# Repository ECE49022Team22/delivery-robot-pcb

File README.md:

# Delivery Robot PCB

KiCad design files for the ECE49022 Team 22 senior design delivery robot control board.

This repository is the shared workspace for the board schematic, PCB layout, project libraries and design documentation.

## System overview

The current schematic includes an STM32F091RC microcontroller core, programming/debug and UART headers, reset and boot circuitry, clock and decoupling components, test points, and power conversion from 12 V to 5 V and 3.3 V. The 12 V input has a fuse, a reverse-battery P-FET, a TVS and a battery-voltage sense. The board also feeds four 5 V peripheral ports, a latch servo (half-duplex UART plus a fused battery feed), two MDD20A motor channels and two encoders, and links to the Raspberry Pi 5 (UART, AUX enable from the Pi 3V3, STM32 reset and BOOT0). An INA237 measures battery current on an off-board shunt (firmware counts charge) in the battery negative lead, and a buffered 5 V data line drives the payload-compartment WS2812B interior light.

The IMU (BNO085) is not on this board; it is wired to the robot off-board.

## Getting started

1. Install KiCad 10 with its standard symbol and footprint libraries.
2. Clone this repository.
3. Open delivery_robot_1.kicad_pro in KiCad Manager.
4. Open delivery_robot_1.kicad_sch to view the complete schematic. Use the Schematic Hierarchy panel to navigate between sheets.

Custom symbol and footprint libraries are included and registered in the project library tables. Keep the directory structure intact so project-relative library paths resolve.

## Repository contents

| Path | Purpose |
| --- | --- |
| delivery_robot_1.kicad_pro | Active KiCad project settings |
| delivery_robot_1.kicad_sch | Main board schematic |
| Buck_5V_2A.kicad_sch | Hierarchical 12 V to 5 V, 2 A buck sheet (TPS54202H, U3) |
| Buck_5V_6A.kicad_sch | Hierarchical 12 V to 5 V, 6 A buck sheet (TPS56637, U2), feeds the Pi 5 |
| Buck_5V_6A_AUX.kicad_sch | Second 12 V to 5 V, 6 A buck sheet (TPS56637, U5), +5V_AUX rail |
| LDO_3V3.kicad_sch | Hierarchical 3.3 V power supply sheet |
| Pi5_Interface.kicad_sch | Raspberry Pi 5 link J13 (6-pin JST XH: UART via R12/R13 1k, GND, Pi 3V3 for the AUX enable, STM32 reset Q2, BOOT0) and Pi power output J14 |
| GPIO_Breakout.kicad_sch | 2x8 2.54 mm expansion header J8 with spare MCU pins only: 1 +3V3, 2/16 GND, ADC (PC0/PA1/PA4), SPI2 (PB13 SCK, PC2 MISO, PB15 MOSI, PB9 CS), PWM (PC6/PC7), USART3 (PC10/PC11), I2C1 (PB6/PB7, now a shared bus with on-board 4.7k pull-ups R56/R57 and the INA237 U13 at 0x40). Unused MCU pins are no-connect. |
| Power_Indicators.kicad_sch | Green power LED per rail (+12V, +5V_PI, +5V_AUX, +5V_SYS, +3V3) and yellow STM32 debug LEDs (PA5, PB12, PB14) |
| Motor_Control.kicad_sch | MDD20A driver terminals (J6, J16) and encoder terminals (J7, J15) for two motors, PWM pull-downs, PTC on each driver ground, encoder buffers U9/U10 (74LVC2G17) with 1k + 1 nF filters, PTC-protected encoder supplies, USBLC6-4SC6 ESD arrays U6 (J6 + J16) and U7 (J7 + J15), STM32 pin table |
| Test_Points.kicad_sch | Power test points: J5 1x06 2.54 mm header (+12V, GND, +5V_AUX, +5V_SYS, +3V3, +3.3VA) and TP3 scope GND loop |
| Input_Protection.kicad_sch | Reverse-battery P-FET Q1 with gate clamp, SMBJ16A TVS D13 on +12V, battery-voltage divider to PA0 |
| AUX_Outputs.kicad_sch | Four +5V_AUX peripheral ports J18-J21 (top-entry JST XH), one 1.5 A PTC each |
| Servo_Interface.kicad_sch | Latch servo port J17 (fused battery feed for an external buck, half-duplex UART through U8 SN74LVC1T45) |
| Battery_Monitor.kicad_sch | Battery current monitor: U13 INA237 on an off-board 50 A / 75 mV shunt in the battery - lead (Kelvin sense on J23), 10R/100 nF input filter, I2C1 on PB6/PB7 at 0x40, ALERT to PB4, VBUS on +12V |
| Interior_Light.kicad_sch | Payload-compartment WS2812B light J24 (3-pin top-entry JST XH): +5V_AUX through PTC F12, U14 SN74LV1T125 buffers PB5 (SPI1_MOSI) data to 5 V, D16 ESD |
| delivery_robot_1.pdf | Plot of all schematic sheets, regenerated automatically on every schematic commit |
| tools/hooks/ | Git hooks (pre-commit regenerates the schematic PDF) |
| libs/ | Project libraries: custom buck converter symbols/footprints, and project_symbols.kicad_sym (STM32F091RCTx and Crystal_GND24 frozen at the versions this design uses) |
| LDO_KiCad/ | Reusable LDO example, libraries and footprint review |
| sym-lib-table, fp-lib-table | Project-specific library configuration |
| docs/ | Subsystem documentation and design notes |
| validation/ | Connectivity checks and reference netlist |
| system-ERC-report.txt | Saved electrical rules check results |
| system-netlist.xml | Exported system connectivity |
| system-preview/ | Rendered schematic sheets |
| received-project-settings/ | Archived initial settings; not the active project |

Power supply details are documented in [docs/power-supply.md](docs/power-supply.md). Earlier simulation notes are in [STM32-LDO-design.md](STM32-LDO-design.md).

The 2026-10-15 design review changes are summarized in [docs/design-review-2026-10-15.md](docs/design-review-2026-10-15.md). The 2026-10-27 battery current monitor and interior light are described in [docs/design-change-2026-10-27.md](docs/design-change-2026-10-27.md).

Component-selection rationale is in [docs/passive-selection-review.md](docs/passive-selection-review.md), [docs/clock-selection.md](docs/clock-selection.md) and [docs/fuse-selection.md](docs/fuse-selection.md). The fuse selection includes both the PCB-mounted holder and its separately purchased insert.

## Design status

Schematic: ERC is clean (0 errors, 0 warnings). PCB: 100 x 100 mm, 4 layers with an In1 GND plane. The board was fully routed as of commit 789cabe (2026-10-26), including outer-layer GND pours with stitching vias and widened high-current paths.

The `feat/battery-monitor-interior-light` branch (2026-10-27) added 18 parts: U13, U14, J23, J24, F12, D16, R54-R60 and C52-C56. They are placed and routed. DRC is clean, with 0 unconnected and 0 schematic parity issues. Layout notes are in [docs/design-change-2026-10-27.md](docs/design-change-2026-10-27.md#layout).

The saved ERC report and netlist (system-ERC-report.txt, system-netlist.xml) were regenerated on 2026-10-28 with KiCad 10.0.6 for the INA237 / 5.10 V change (ERC: 0 errors, 0 warnings). validation/verify_2026_10_27.py checks the branch against the netlist of its parent commit. validation/verify_integration.py checks against the older October 5 connectivity.

Saved reports describe the checked revision. Regenerate them after relevant design changes.

## Team workflow

- Use the active delivery_robot_1 project for board work.
- Pull current changes before editing and coordinate ownership of schematic sheets and the PCB.
- Work on branches and review changes before merging.
- Save files in KiCad before committing. Include required project-local libraries with design changes.
- Run ERC after schematic changes and DRC after layout changes. Review outstanding findings before ordering boards.
- Enable the repository hooks once per clone with `git config core.hooksPath tools/hooks`. The pre-commit hook then re-plots delivery_robot_1.pdf from the staged schematic files and adds it to any commit that changes a `.kicad_sch` or `.kicad_pro` file. It needs KiCad installed; set `KICAD_CLI` if kicad-cli is not in the default location.

Editing locks, local UI settings and automatic backups are excluded from Git. Edit the native KiCad sources directly; regenerating files from older scripts may overwrite manual changes.

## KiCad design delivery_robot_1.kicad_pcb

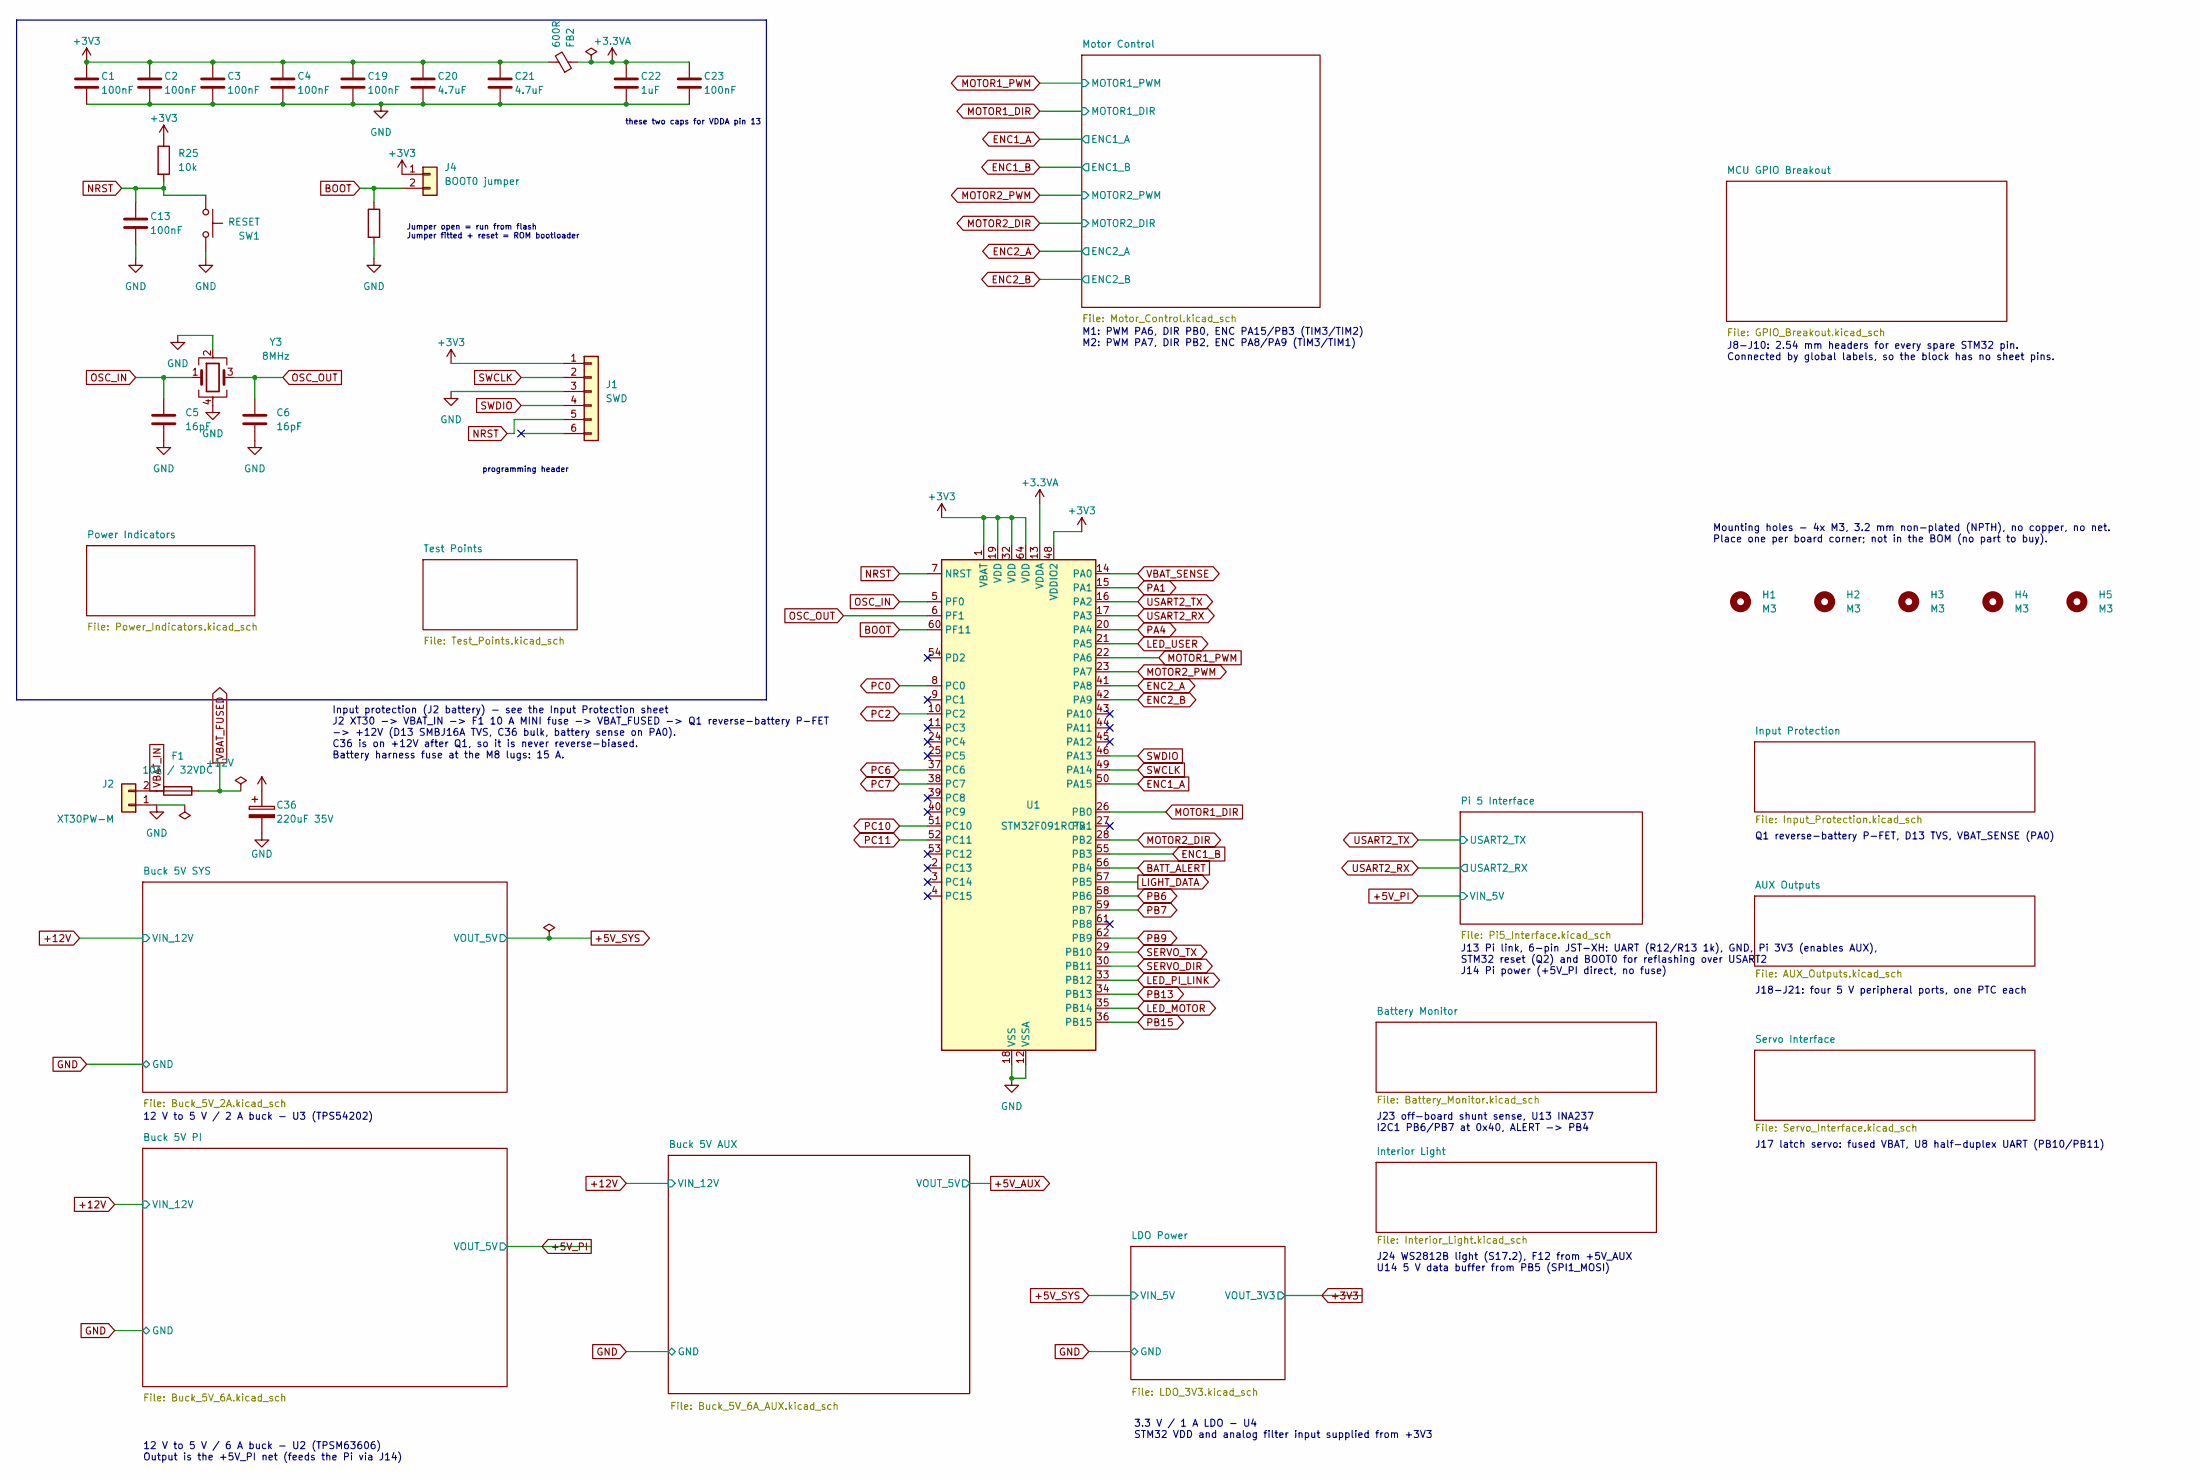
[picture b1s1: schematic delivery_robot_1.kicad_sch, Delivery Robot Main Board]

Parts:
C1, C2, C3, C4, C13, C19, C23: 100nF; C_0805_2012Metric
C5, C6: 16pF; C_0805_2012Metric; MPN C0805C160J5GACTU
C20, C21: 4.7uF; C_0805_2012Metric
C22: 1uF; C_0805_2012Metric
C36: 220uF 35V; CP_Radial_D8.0mm_P3.50mm; MPN EEU-FR1V221
F1: 10A / 32VDC; Fuseholder_Blade_Mini_Keystone_3568; MPN 3568
FB2: 600R; L_0805_2012Metric; MPN BLM21PG601SN1D
H1, H2, H3, H4, H5: M3; MountingHole_3.2mm_M3
J1: SWD; PinHeader_1x06_P2.54mm_Vertical
J2: XT30PW-M; AMASS_XT30PW-M_1x02_P2.50mm_Horizontal; MPN XT30PW-M
J4: BOOT0 jumper; PinHeader_1x02_P2.54mm_Vertical
R1, R25: 10k; R_0805_2012Metric
SW1: RESET; SW_SPST_PTS810
U1: STM32F091RCTx; LQFP-64_10x10mm_P0.5mm
Y3: 8MHz; Crystal_SMD_Abracon_ABM3B-4Pin_5.0x3.2mm; MPN ABM3B-8.000MHZ-B2-T

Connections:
+3.3VA: C22.1, C23.1, FB2.1, U1.13 (VDDA); also elsewhere on the board
+3V3: C1.1, C2.1, C3.1, C4.1, C19.1, C20.1, C21.1, FB2.2, J1.1, J4.1, R25.1, U1.1 (VBAT), U1.19 (VDD), U1.32 (VDD), U1.48 (VDDIO2), U1.64 (VDD); also elsewhere on the board
+12V: C36.1; also elsewhere on the board
BATT_ALERT: U1.56 (PB4); also elsewhere on the board
BOOT: J4.2, R1.1, U1.60 (PF11); also elsewhere on the board
ENC1_A: U1.50 (PA15); also elsewhere on the board
ENC1_B: U1.55 (PB3); also elsewhere on the board
ENC2_A: U1.41 (PA8); also elsewhere on the board
ENC2_B: U1.42 (PA9); also elsewhere on the board
GND: C1.2, C2.2, C3.2, C4.2, C5.2, C6.2, C13.2, C19.2, C20.2, C21.2, C22.2, C23.2, C36.2, J1.3, J2.1, R1.2, SW1.2, U1.12 (VSSA), U1.18 (VSS), U1.31 (VSS), U1.47 (VSS), U1.63 (VSS), Y3.2, Y3.4; also elsewhere on the board
LED_MOTOR: U1.35 (PB14); also elsewhere on the board
LED_PI_LINK: U1.33 (PB12); also elsewhere on the board
LED_USER: U1.21 (PA5); also elsewhere on the board
LIGHT_DATA: U1.57 (PB5); also elsewhere on the board
MOTOR1_DIR: U1.26 (PB0); also elsewhere on the board
MOTOR1_PWM: U1.22 (PA6); also elsewhere on the board
MOTOR2_DIR: U1.28 (PB2); also elsewhere on the board
MOTOR2_PWM: U1.23 (PA7); also elsewhere on the board
NRST: C13.1, J1.5, R25.2, SW1.1, U1.7 (NRST); also elsewhere on the board
OSC_IN: C5.1, U1.5 (PF0), Y3.1
OSC_OUT: C6.1, U1.6 (PF1), Y3.3
PA1: U1.15 (PA1); also elsewhere on the board
PA4: U1.20 (PA4); also elsewhere on the board
PB6: U1.58 (PB6); also elsewhere on the board
PB7: U1.59 (PB7); also elsewhere on the board
PB9: U1.62 (PB9); also elsewhere on the board
PB13: U1.34 (PB13); also elsewhere on the board
PB15: U1.36 (PB15); also elsewhere on the board
PC0: U1.8 (PC0); also elsewhere on the board
PC2: U1.10 (PC2); also elsewhere on the board
PC6: U1.37 (PC6); also elsewhere on the board
PC7: U1.38 (PC7); also elsewhere on the board
PC10: U1.51 (PC10); also elsewhere on the board
PC11: U1.52 (PC11); also elsewhere on the board
SERVO_DIR: U1.30 (PB11); also elsewhere on the board
SERVO_TX: U1.29 (PB10); also elsewhere on the board
SWCLK: J1.2, U1.49 (PA14)
SWDIO: J1.4, U1.46 (PA13)
USART2_RX: U1.17 (PA3); also elsewhere on the board
USART2_TX: U1.16 (PA2); also elsewhere on the board
VBAT_FUSED: F1.1; also elsewhere on the board
VBAT_IN: F1.2, J2.2
VBAT_SENSE: U1.14 (PA0); also elsewhere on the board

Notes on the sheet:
J24 WS2812B light (S17.2), F12 from +5V_AUX U14 5 V data buffer from PB5 (SPI1_MOSI)
J13 Pi link, 6-pin JST-XH: UART (R12/R13 1k), GND, Pi 3V3 (enables AUX), STM32 reset (Q2) and BOOT0 for reflashing over USART2 J14 Pi power (+5V_PI direct, no fuse)
Jumper open = run from flash Jumper fitted + reset = ROM bootloader
J17 latch servo: fused VBAT, U8 half-duplex UART (PB10/PB11)
M1: PWM PA6, DIR PB0, ENC PA15/PB3 (TIM3/TIM2) M2: PWM PA7, DIR PB2, ENC PA8/PA9 (TIM3/TIM1)
programming header
J18-J21: four 5 V peripheral ports, one PTC each
3.3 V / 1 A LDO - U4 STM32 VDD and analog filter input supplied from +3V3
J8-J10: 2.54 mm headers for every spare STM32 pin. Connected by global labels, so the block has no sheet pins.
J23 off-board shunt sense, U13 INA237 I2C1 PB6/PB7 at 0x40, ALERT -> PB4
Mounting holes - 4x M3, 3.2 mm non-plated (NPTH), no copper, no net. Place one per board corner; not in the BOM (no part to buy).
Q1 reverse-battery P-FET, D13 TVS, VBAT_SENSE (PA0)
these two caps for VDDA pin 13
Input protection (J2 battery) - see the Input Protection sheet J2 XT30 -> VBAT_IN -> F1 10 A MINI fuse -> VBAT_FUSED -> Q1 reverse-battery P-FET -> +12V (D13 SMBJ16A TVS, C36 bulk, battery sense on PA0). C36 is on +12V after Q1, so it is never reverse-biased. Battery harness fuse at the M8 lugs: 15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
12 V to 5 V / 2 A buck - U3 (TPS54202)
12 V to 5 V / 6 A buck - U2 (TPSM63606) Output is the +5V_PI net (feeds the Pi via J14)

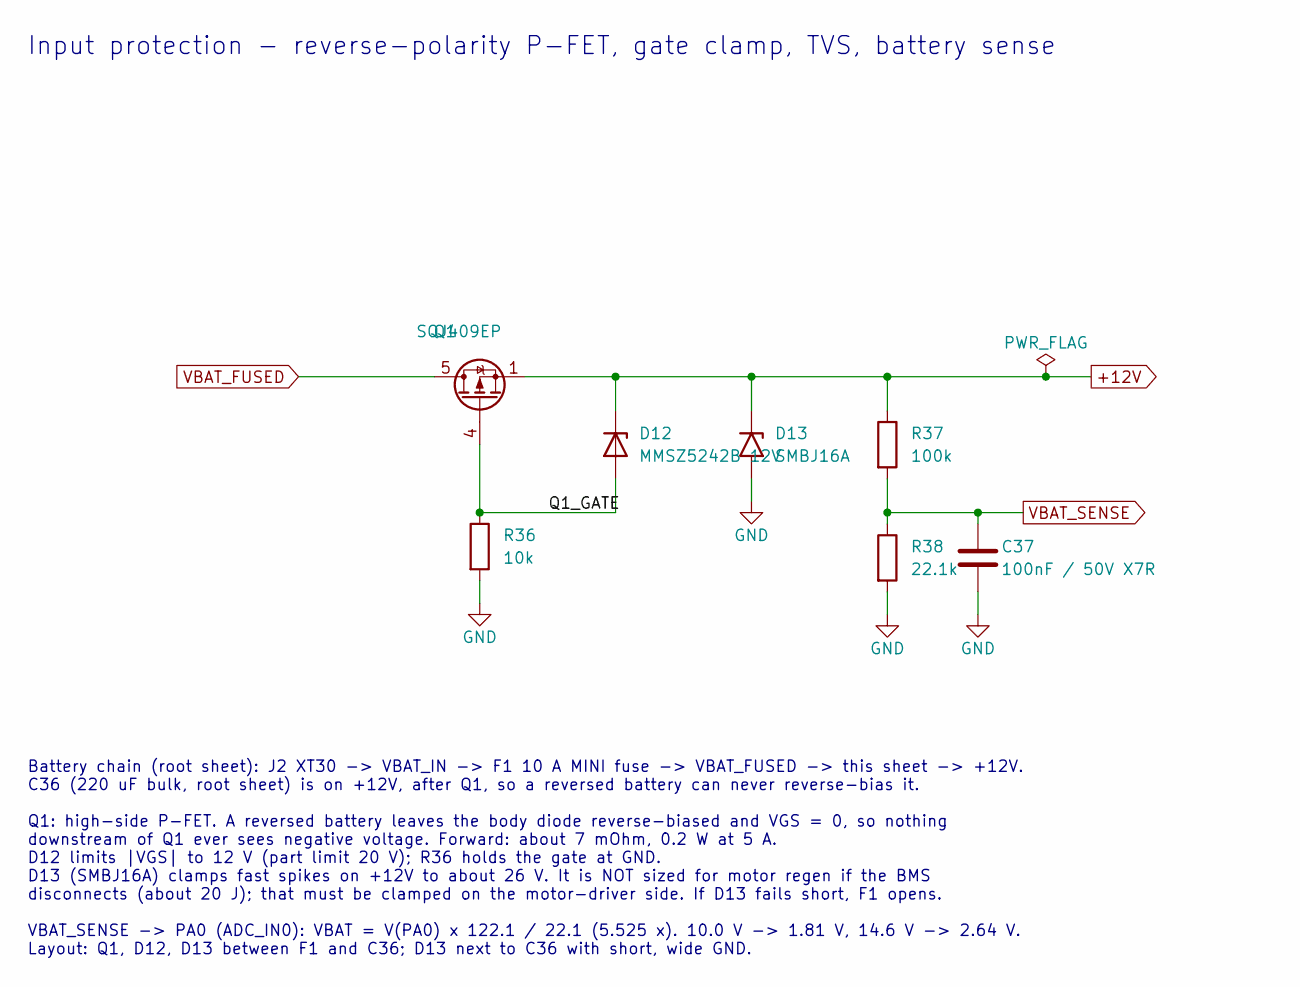
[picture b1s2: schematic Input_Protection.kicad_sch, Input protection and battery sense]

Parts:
C37: 100nF / 50V X7R; C_0805_2012Metric; MPN C0805C104K5RACTU
D12: MMSZ5242B 12V; D_SOD-123; MPN MMSZ5242BT1G
D13: SMBJ16A; D_SMB; MPN SMBJ16A
Q1: SQJ409EP; PowerPAK_SO-8L_Single; MPN SQJ409EP-T1_BE3
R36: 10k; R_0805_2012Metric
R37: 100k; R_0805_2012Metric; Tolerance 1%
R38: 22.1k; R_0805_2012Metric; Tolerance 1%

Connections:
+12V: D12.1 (K), D13.1 (A1), Q1.1 (S), Q1.2 (S), Q1.3 (S), R37.1; also elsewhere on the board
/Input Protection/Q1_GATE: D12.2 (A), Q1.4 (G), R36.1
GND: C37.2, D13.2 (A2), R36.2, R38.2; also elsewhere on the board
VBAT_FUSED: Q1.5 (D); also elsewhere on the board
VBAT_SENSE: C37.1, R37.2, R38.1; also elsewhere on the board

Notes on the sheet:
Battery chain (root sheet): J2 XT30 -> VBAT_IN -> F1 10 A MINI fuse -> VBAT_FUSED -> this sheet -> +12V. C36 (220 uF bulk, root sheet) is on +12V, after Q1, so a reversed battery can never reverse-bias it. Q1: high-side P-FET. A reversed battery leaves the body diode reverse-biased and VGS = 0, so 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
Input protection - reverse-polarity P-FET, gate clamp, TVS, battery sense

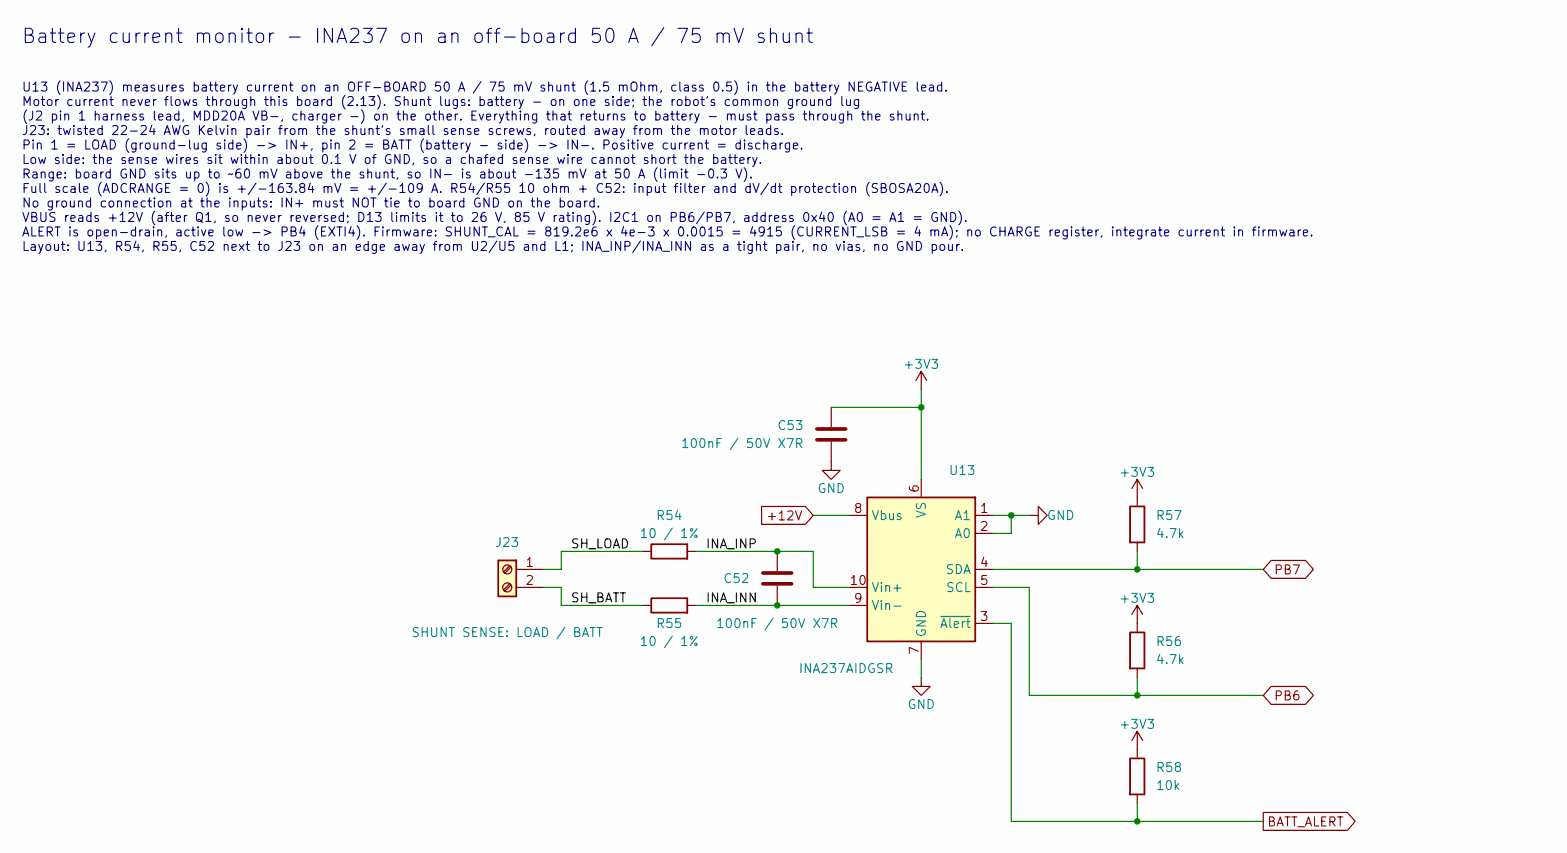
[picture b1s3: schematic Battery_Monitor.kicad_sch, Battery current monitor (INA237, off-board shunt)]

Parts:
C52, C53: 100nF / 50V X7R; C_0805_2012Metric; MPN C0805C104K5RACTU
J23: SHUNT SENSE: LOAD / BATT; TerminalBlock_Phoenix_MPT-0,5-2-2.54_1x02_P2.54mm_Horizontal; MPN 1725656
R54, R55: 10 / 1%; R_0805_2012Metric; Tolerance 1%; MPN RC0805FR-0710RL
R56, R57: 4.7k; R_0805_2012Metric; Tolerance 1%; MPN RC0805FR-074K7L
R58: 10k; R_0805_2012Metric; Tolerance 1%; MPN RC0805FR-0710KL
U13: INA237AIDGSR; TSSOP-10_3x3mm_P0.5mm; MPN INA237AIDGSR

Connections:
+3V3: C53.1, R56.1, R57.1, R58.1, U13.6 (VS); also elsewhere on the board
+12V: U13.8 (Vbus); also elsewhere on the board
/Battery Monitor/INA_INN: C52.2, R55.2, U13.9 (Vin-)
/Battery Monitor/INA_INP: C52.1, R54.2, U13.10 (Vin+)
/Battery Monitor/SH_BATT: J23.2, R55.1
/Battery Monitor/SH_LOAD: J23.1, R54.1
BATT_ALERT: R58.2, U13.3 (~Alert); also elsewhere on the board
GND: C53.2, U13.1 (A1), U13.2 (A0), U13.7 (GND); also elsewhere on the board
PB6: R56.2, U13.5 (SCL); also elsewhere on the board
PB7: R57.2, U13.4 (SDA); also elsewhere on the board

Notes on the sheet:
Battery current monitor - INA237 on an off-board 50 A / 75 mV shunt
U13 (INA237) measures battery current on an OFF-BOARD 50 A / 75 mV shunt (1.5 mOhm, class 0.5) in the battery NEGATIVE lead. Motor current never flows through this board (2.13). Shunt lugs: battery - on one side; the robot's common ground lug (J2 pin 1 harness lead, MDD20A VB-, charger -) on the ot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

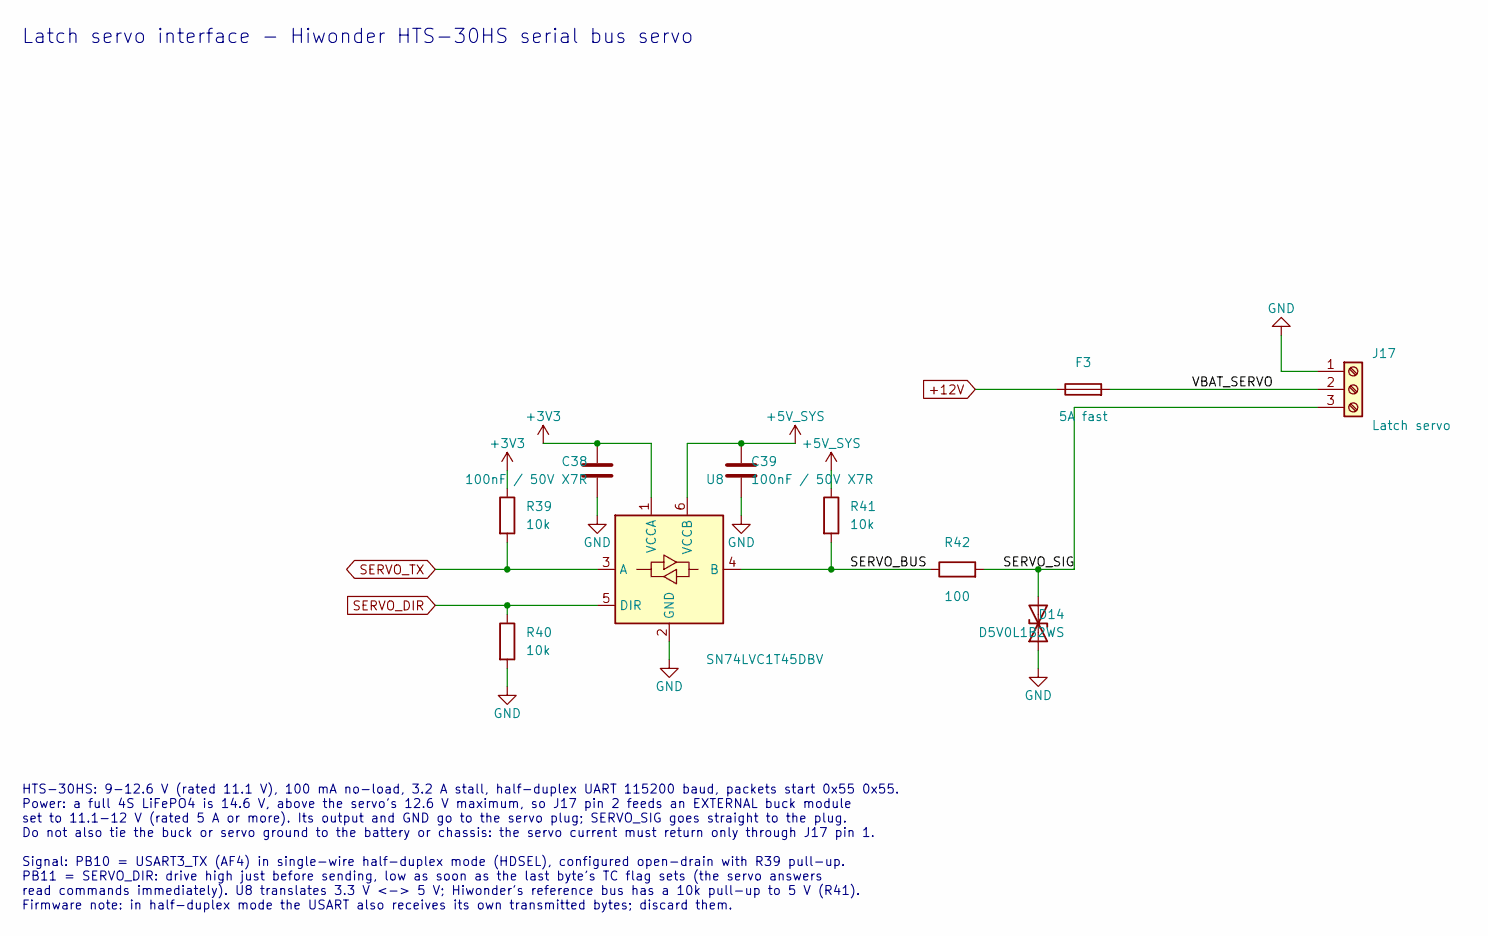
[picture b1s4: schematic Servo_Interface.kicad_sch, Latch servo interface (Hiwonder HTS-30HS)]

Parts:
C38, C39: 100nF / 50V X7R; C_0805_2012Metric; MPN C0805C104K5RACTU
D14: D5V0L1B2WS; D_SOD-323; MPN D5V0L1B2WS-7
F3: 5A fast; Fuse_Littelfuse-NANO2-451_453; MPN 0451005.MRL
J17: Latch servo; TerminalBlock_Phoenix_MKDS-1,5-3_1x03_P5.00mm_Horizontal; MPN 1715035 (MKDS 1,5/3, 5.0 mm pitch)
R39, R40, R41: 10k; R_0805_2012Metric
R42: 100; R_0805_2012Metric
U8: SN74LVC1T45DBV; SOT-23-6; MPN SN74LVC1T45DBVR

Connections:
+3V3: C38.1, R39.1, U8.1 (VCCA); also elsewhere on the board
+5V_SYS: C39.1, R41.1, U8.6 (VCCB); also elsewhere on the board
+12V: F3.1; also elsewhere on the board
/Servo Interface/SERVO_BUS: R41.2, R42.1, U8.4 (B)
/Servo Interface/SERVO_SIG: D14.2 (A2), J17.3, R42.2
/Servo Interface/VBAT_SERVO: F3.2, J17.2
GND: C38.2, C39.2, D14.1 (A1), J17.1, R40.2, U8.2 (GND); also elsewhere on the board
SERVO_DIR: R40.1, U8.5 (DIR); also elsewhere on the board
SERVO_TX: R39.2, U8.3 (A); also elsewhere on the board

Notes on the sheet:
Latch servo interface - Hiwonder HTS-30HS serial bus servo
HTS-30HS: 9-12.6 V (rated 11.1 V), 100 mA no-load, 3.2 A stall, half-duplex UART 115200 baud, packets start 0x55 0x55. Power: a full 4S LiFePO4 is 14.6 V, above the servo's 12.6 V maximum, so J17 pin 2 feeds an EXTERNAL buck module set to 11.1-12 V (rated 5 A or more). Its output and GND go to the 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

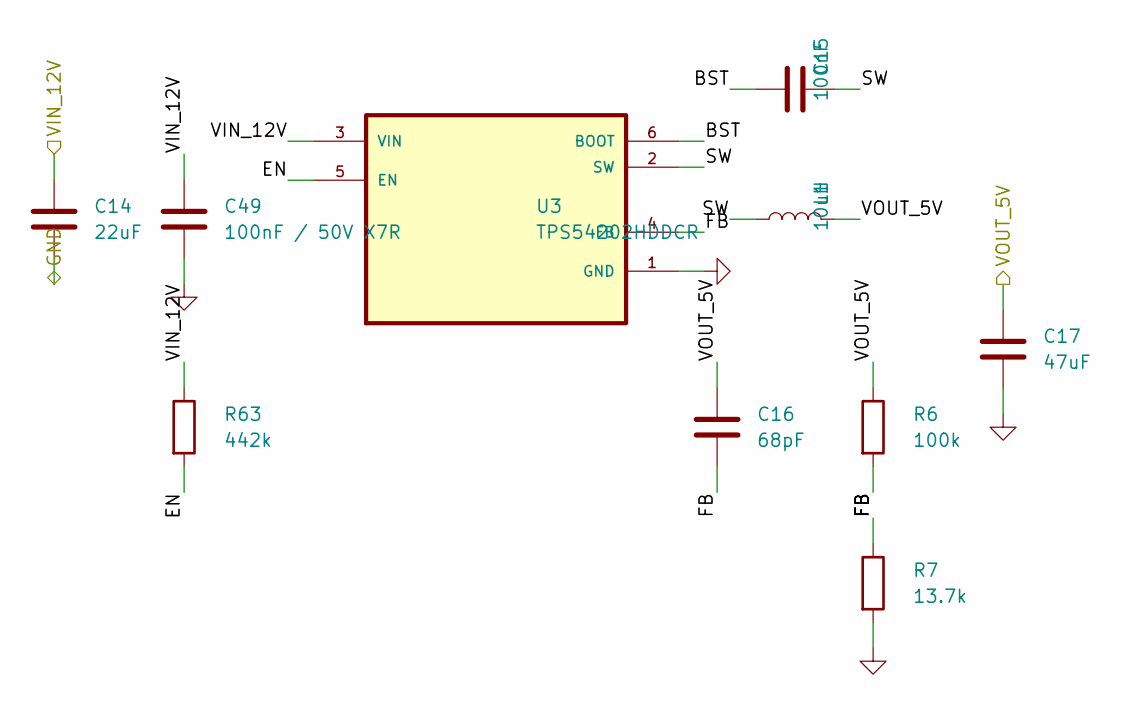
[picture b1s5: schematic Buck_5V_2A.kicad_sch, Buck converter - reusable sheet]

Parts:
C14: 22uF; C_1210_3225Metric; MPN GRM32ER61E226KE15L
C15: 100nF; C_0805_2012Metric; MPN C0805C104K5RACTU
C16: 68pF; C_0805_2012Metric; MPN C0805C680J5GACTU
C17: 47uF; C_1210_3225Metric; MPN GRM32ER61C476KE15L
C49: 100nF / 50V X7R; C_0805_2012Metric; MPN C0805C104K5RACTU
L1: 10uH; L_TDK_VLS6045EX_VLS6045AF; MPN VLS6045EX-100M
R6: 100k; R_0805_2012Metric; MPN RC0805FR-07100KL
R7: 13.7k; R_0805_2012Metric; MPN RC0805FR-0713K7L
R63: 442k; R_0805_2012Metric; MPN RC0805FR-07442KL
U3: TPS54202HDDCR; SOT95P280X110-6N; MPN TPS54202HDDCR

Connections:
+5V_SYS: C16.1, C17.1, L1.2, R6.1; also elsewhere on the board
+12V: C14.1, C49.1, R63.1, U3.3 (VIN); also elsewhere on the board
/Buck 5V SYS/BST: C15.1, U3.6 (BOOT)
/Buck 5V SYS/EN: R63.2, U3.5 (EN)
/Buck 5V SYS/FB: C16.2, R6.2, R7.1, U3.4 (FB)
/Buck 5V SYS/SW: C15.2, L1.1, U3.2 (SW)
GND: C14.2, C17.2, C49.2, R7.2, U3.1 (GND); also elsewhere on the board

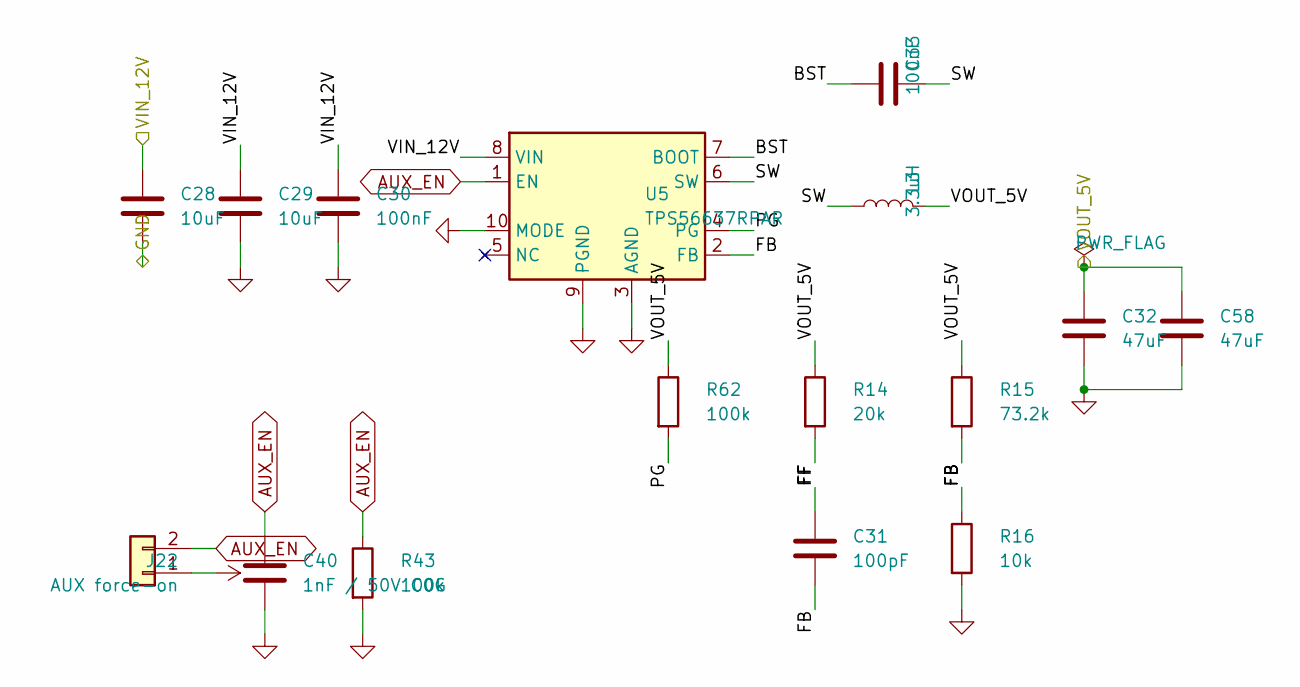
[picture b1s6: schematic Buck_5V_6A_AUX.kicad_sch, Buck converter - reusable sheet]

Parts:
C28, C29: 10uF; C_1206_3216Metric; MPN GRM31CR71E106KA12L
C30, C33: 100nF; C_0805_2012Metric; MPN C0805C104K5RACTU
C31: 100pF; C_0805_2012Metric; MPN C0805C101J5GACTU
C32, C58: 47uF; C_1210_3225Metric; MPN GRM32ER61C476KE15L
C40: 1nF / 50V C0G; C_0805_2012Metric; MPN C0805C102J5GACTU
J22: AUX force-on; PinHeader_1x02_P2.54mm_Vertical
L3: 3.3uH; L_Wuerth_WE-XHMI-7070; MPN 74439387033
R14: 20k; R_0805_2012Metric; MPN ERJ-6ENF2002V
R15: 73.2k; R_0805_2012Metric; MPN RC0805FR-0773K2L
R16: 10k; R_0805_2012Metric; MPN RC0805FR-0710KL
R43: 100k; R_0805_2012Metric
R62: 100k; R_0805_2012Metric; MPN RC0805FR-07100KL
U5: TPS56637RPAR; TI_RPA0010A_VQFN-HR-10_3x3mm; MPN TPS56637RPAR

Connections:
+3V3: J22.1; also elsewhere on the board
+5V_AUX: C32.1, C58.1, L3.2, R14.1, R15.1, R62.1; also elsewhere on the board
+12V: C28.1, C29.1, C30.1, U5.8 (VIN); also elsewhere on the board
/Buck 5V AUX/BST: C33.1, U5.7 (BOOT)
/Buck 5V AUX/FB: C31.2, R15.2, R16.1, U5.2 (FB)
/Buck 5V AUX/FF: C31.1, R14.2
/Buck 5V AUX/PG: R62.2, U5.4 (PG)
/Buck 5V AUX/SW: C33.2, L3.1, U5.6 (SW)
AUX_EN: C40.1, J22.2, R43.1, U5.1 (EN); also elsewhere on the board
GND: C28.2, C29.2, C30.2, C32.2, C40.2, C58.2, R16.2, R43.2, U5.3 (AGND), U5.9 (PGND), U5.10 (MODE); also elsewhere on the board

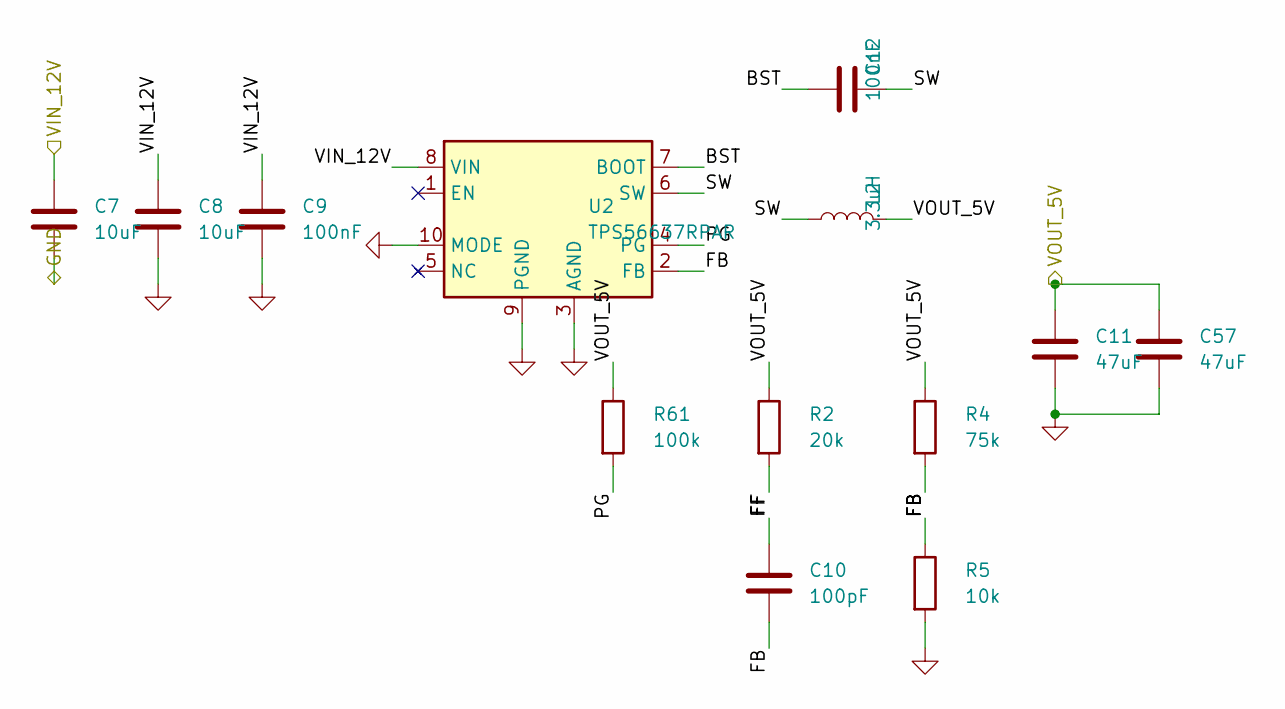
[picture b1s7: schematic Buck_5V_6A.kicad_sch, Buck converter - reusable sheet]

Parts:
C7, C8: 10uF; C_1206_3216Metric; MPN GRM31CR71E106KA12L
C9, C12: 100nF; C_0805_2012Metric; MPN C0805C104K5RACTU
C10: 100pF; C_0805_2012Metric; MPN C0805C101J5GACTU
C11, C57: 47uF; C_1210_3225Metric; MPN GRM32ER61C476KE15L
L2: 3.3uH; L_Wuerth_WE-XHMI-7070; MPN 74439387033
R2: 20k; R_0805_2012Metric; MPN ERJ-6ENF2002V
R4: 75k; R_0805_2012Metric; MPN RC0805FR-0775KL
R5: 10k; R_0805_2012Metric; MPN RC0805FR-0710KL
R61: 100k; R_0805_2012Metric; MPN RC0805FR-07100KL
U2: TPS56637RPAR; TI_RPA0010A_VQFN-HR-10_3x3mm; MPN TPS56637RPAR

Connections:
+5V_PI: C11.1, C57.1, L2.2, R2.1, R4.1, R61.1; also elsewhere on the board
+12V: C7.1, C8.1, C9.1, U2.8 (VIN); also elsewhere on the board
/Buck 5V PI/BST: C12.1, U2.7 (BOOT)
/Buck 5V PI/FB: C10.2, R4.2, R5.1, U2.2 (FB)
/Buck 5V PI/FF: C10.1, R2.2
/Buck 5V PI/PG: R61.2, U2.4 (PG)
/Buck 5V PI/SW: C12.2, L2.1, U2.6 (SW)
GND: C7.2, C8.2, C9.2, C11.2, C57.2, R5.2, U2.3 (AGND), U2.9 (PGND), U2.10 (MODE); also elsewhere on the board

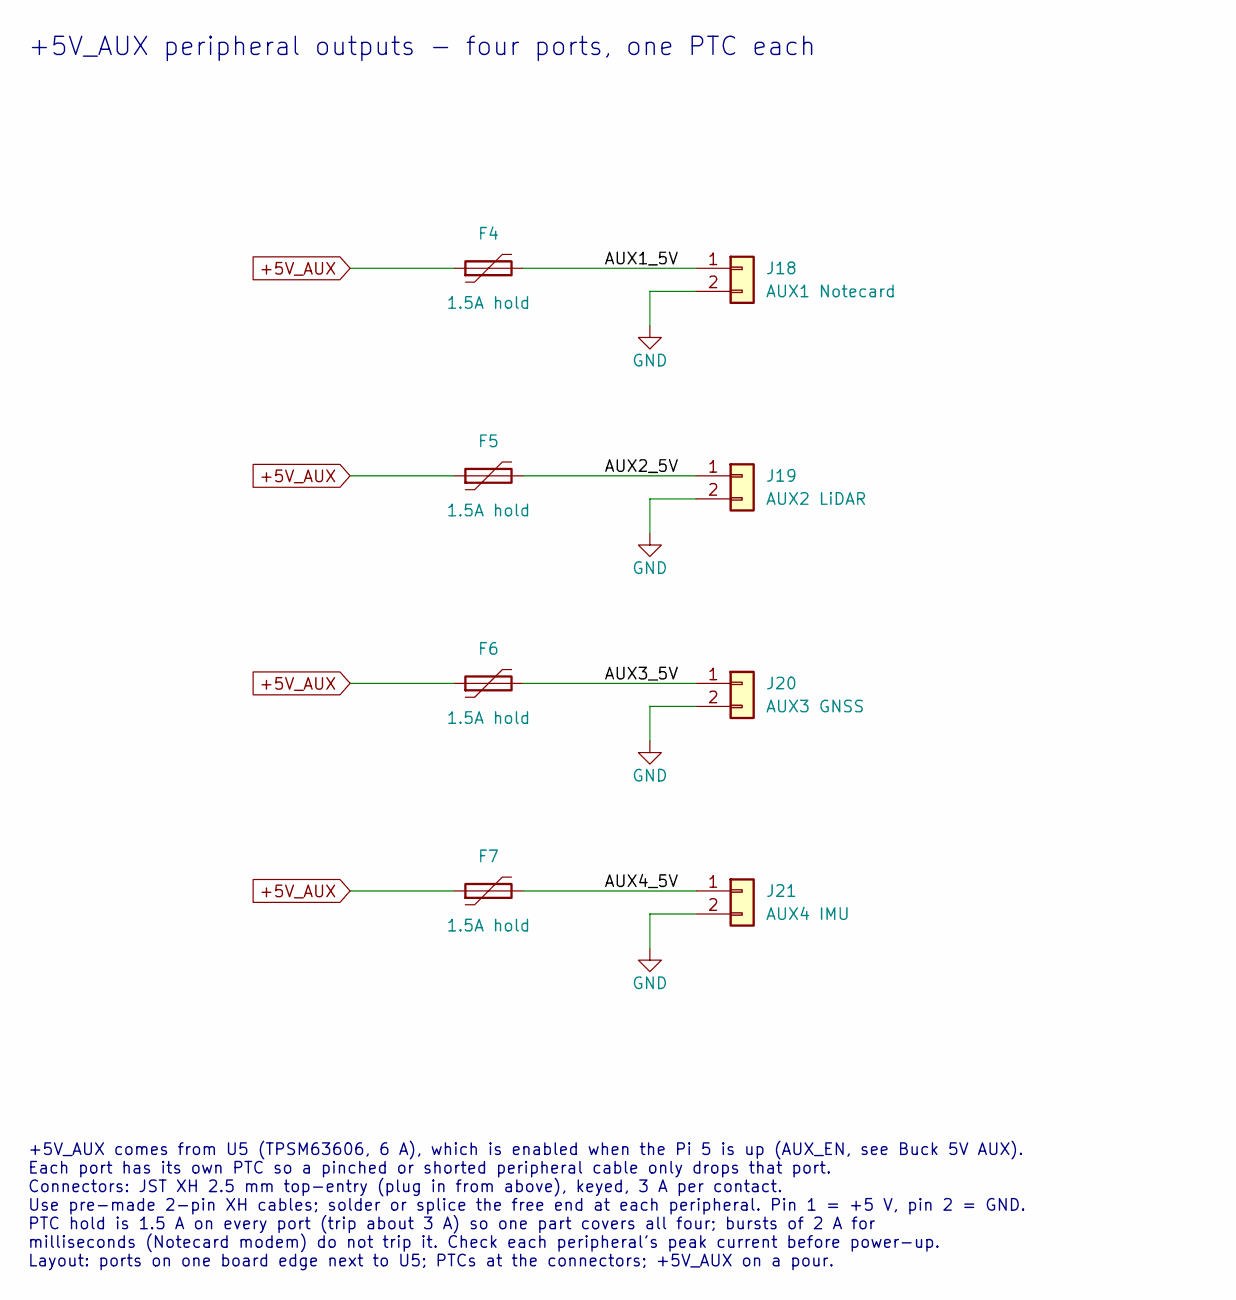
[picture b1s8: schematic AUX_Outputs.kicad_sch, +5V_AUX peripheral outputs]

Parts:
F4, F5, F6, F7: 1.5A hold; Fuse_1812_4532Metric; MPN 1812L150/16DR
J18: AUX1 Notecard; JST_XH_B2B-XH-A_1x02_P2.50mm_Vertical; MPN B2B-XH-A(LF)(SN)
J19: AUX2 LiDAR; JST_XH_B2B-XH-A_1x02_P2.50mm_Vertical; MPN B2B-XH-A(LF)(SN)
J20: AUX3 GNSS; JST_XH_B2B-XH-A_1x02_P2.50mm_Vertical; MPN B2B-XH-A(LF)(SN)
J21: AUX4 IMU; JST_XH_B2B-XH-A_1x02_P2.50mm_Vertical; MPN B2B-XH-A(LF)(SN)

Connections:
+5V_AUX: F4.1, F5.1, F6.1, F7.1; also elsewhere on the board
/AUX Outputs/AUX1_5V: F4.2, J18.1
/AUX Outputs/AUX2_5V: F5.2, J19.1
/AUX Outputs/AUX3_5V: F6.2, J20.1
/AUX Outputs/AUX4_5V: F7.2, J21.1
GND: J18.2, J19.2, J20.2, J21.2; also elsewhere on the board

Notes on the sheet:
+5V_AUX peripheral outputs - four ports, one PTC each
+5V_AUX comes from U5 (TPSM63606, 6 A), which is enabled when the Pi 5 is up (AUX_EN, see Buck 5V AUX). Each port has its own PTC so a pinched or shorted peripheral cable only drops that port. Connectors: JST XH 2.5 mm top-entry (plug in from above), keyed, 3 A per contact. Use pre-made 2-pin XH ca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

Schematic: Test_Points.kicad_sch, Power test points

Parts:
J5: Power test points; PinHeader_1x06_P2.54mm_Vertical
TP3: GND; TestPoint_Keystone_5010-5014_Multipurpose; MPN 5011 (black multipurpose test point)

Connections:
+3.3VA: J5.6; also elsewhere on the board
+3V3: J5.5; also elsewhere on the board
+5V_AUX: J5.3; also elsewhere on the board
+5V_SYS: J5.4; also elsewhere on the board
+12V: J5.1; also elsewhere on the board
GND: J5.2, TP3.1 (1_1); also elsewhere on the board

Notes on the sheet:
J5: one 2.54 mm header for every rail 1 +12V (after Q1) 2 GND 3 +5V_AUX 4 +5V_SYS 5 +3V3 6 +3.3VA (MCU analog) +12V is next to GND only.
TP3: GND loop for the scope ground clip. +5V_PI is on TP1 (Pi 5 Interface sheet), used in the Pi bring-up check.
Power test points
